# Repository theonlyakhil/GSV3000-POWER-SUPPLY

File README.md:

# GSV3000-POWER-SUPPLY

18v 30A power supply circuit diagram and KICAD files

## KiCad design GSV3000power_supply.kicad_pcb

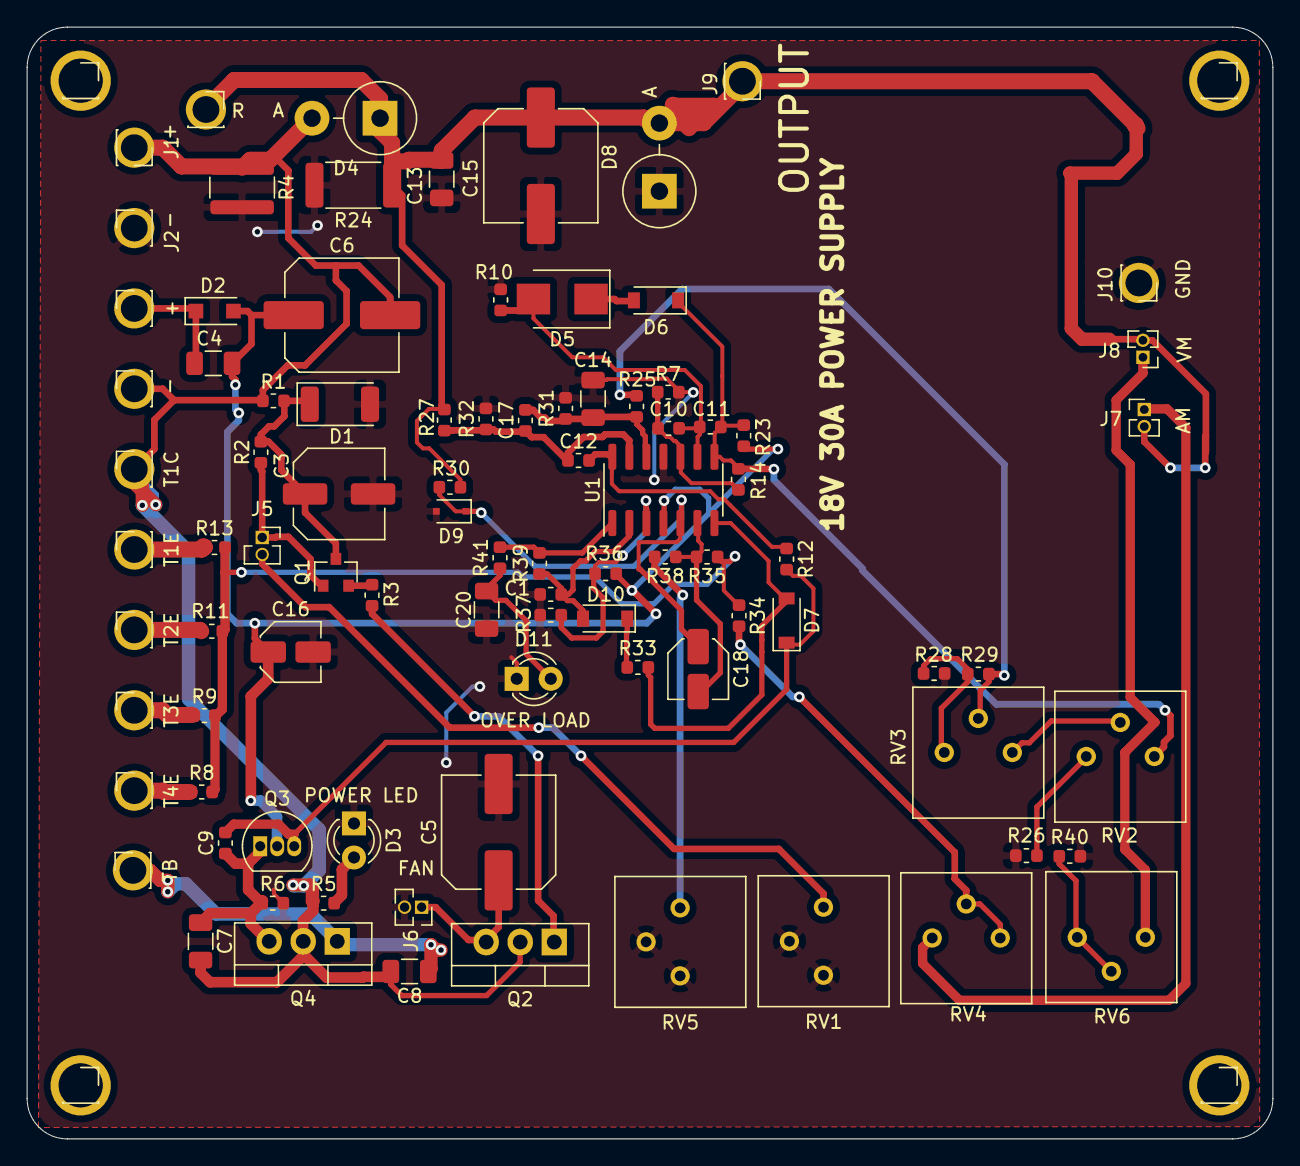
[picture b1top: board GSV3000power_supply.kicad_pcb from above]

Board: 2 copper layers, 93.0 x 83.0 mm, 94 parts (0 on the bottom side), 44 nets.

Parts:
3: 3; PinSocket_1x01_P2.54mm_Vertical
4: 4; PinSocket_1x01_P2.54mm_Vertical
C1: 1UF50V; C_0603_1608Metric
C3: 100uF; C_Elec_6.3x7.7
C4, C7, C13, C14, C20: 0.01uF; C_1206_3216Metric
C5: 220uF 25v; C_Elec_8x10.2
C6: 1000uF; C_Elec_8x10.2
C8: 0.01Uf; C_1206_3216Metric
C9: 100pF; C_0603_1608Metric
C10, C17: 22pF; C_0603_1608Metric
C11: 0.1uF; C_0603_1608Metric
C12: 0.001uF; C_0603_1608Metric
C15: 220uF 25V; C_Elec_8x10.2
C16, C18: 1uF; C_Elec_4x5.4
D1: 15V 1W; D_2010_5025Metric
D2: 1N4001; D_SOD-123F
D3: POWER LED; LED_D3.0mm
D4, D8: 1N5401; D_DO-201_P5.08mm_Vertical_AnodeUp
D5: 7.5V; D_SMB
D6, D7, D10: 1N4148; D_SOD-123
D9: 17V; D_SOD-323F
D11: OVER LOAD; LED_D3.0mm
J1, J4: +; PinSocket_1x01_P2.54mm_Vertical
J2, J3: -; PinSocket_1x01_P2.54mm_Vertical
J5: temp; PinSocket_1x02_P1.27mm_Vertical
J6: FAN; PinSocket_1x02_P1.27mm_Vertical
J7: AM; PinHeader_1x02_P1.27mm_Vertical
J8: VM; PinHeader_1x02_P1.27mm_Vertical
J9: OUTPUT; PinSocket_1x01_P2.54mm_Vertical
J10: GND; PinSocket_1x01_P2.54mm_Vertical
J11: T1C; PinSocket_1x01_P2.54mm_Vertical
J12: R; PinSocket_1x01_P2.54mm_Vertical
J15: TB; PinSocket_1x01_P2.54mm_Vertical
J16: T4E; PinSocket_1x01_P2.54mm_Vertical
J17: T3E; PinSocket_1x01_P2.54mm_Vertical
J18: T2E; PinSocket_1x01_P2.54mm_Vertical
J19: T1E; PinSocket_1x01_P2.54mm_Vertical
Q1: B550C; SOT-23
Q2: TIP31C; TO-220-3_Vertical
Q3: 2SC1815; TO-92_Inline
Q4: 2SD880; TO-220-3_Vertical
R1: 390; R_0603_1608Metric
R2: 120K; R_0603_1608Metric
R3, R7, R10, R33: 1K; R_0603_1608Metric
R4: 1K2W; R_1218_3246Metric
R5: 2.7K; R_0603_1608Metric
R6, R35: 4.7K; R_0603_1608Metric
R8: 10 X4; R_0603_1608Metric
R9, R11, R13: 10; R_0603_1608Metric
R12: 3.3K; R_0603_1608Metric
R14: 2.2K; R_0603_1608Metric
R23, R36, R37: 220K; R_0603_1608Metric
R24: 330 1W; R_2512_6332Metric
R25, R26: 5.6K; R_0603_1608Metric
R27, R32: 10K; R_0603_1608Metric
R28: 560; R_0603_1608Metric
R29: 30K; R_0603_1608Metric
R30: 1.5K; R_0603_1608Metric
R31: 1M; R_0603_1608Metric
R34: 330; R_0603_1608Metric
R38: 100K; R_0603_1608Metric
R39: 82K; R_0603_1608Metric
R40: 33K; R_0603_1608Metric
R41: 22K; R_0603_1608Metric
RV1: 50k; Potentiometer_Bourns_3386P_Vertical
RV2: 5K; Potentiometer_Bourns_3386P_Vertical
RV3, RV6: 10K; Potentiometer_Bourns_3386P_Vertical
RV4: 2K; Potentiometer_Bourns_3386P_Vertical
RV5: 50K; Potentiometer_Bourns_3386P_Vertical
S1: 1; PinSocket_1x01_P2.54mm_Vertical
S2: 2; PinSocket_1x01_P2.54mm_Vertical
U1: LM324; SOIC-14_3.9x8.7mm_P1.27mm

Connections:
GND: C1.2, C3.2, C5.2, C13.2, C14.2, C15.2, C16.2, C20.2, D1.2, D3.1, D8.1, D9.2, D11.1, J2.1, J6.2, J10.1, R4.2, R6.2, R7.2, R10.2, R24.2, R26.2, R28.2, R31.2, R32.2, R37.2, R40.2, RV1.2, RV1.3, RV5.2, RV5.3, U1.11
unnamed: C1.1, D10.2, R39.2, U1.2
unnamed: C3.1, D1.1, Q1.3, R1.2, R2.1
unnamed: C4.2, D2.1, J4.1
unnamed: C5.1, J6.1, Q2.3
unnamed: C6.2, C7.2, C8.2, D4.2, J1.1, J3.1, J11.1, Q2.2, Q4.2, R1.1, R4.1, R5.1
unnamed: C7.1, C9.1, Q3.1, Q4.3, R6.1
unnamed: C8.1, J15.1, Q4.1
unnamed: C9.2, D7.1, Q3.3, R12.2
unnamed: C10.1, R7.1, R14.2, U1.10
unnamed: C10.2, C11.2, D5.2, R10.1, U1.9
unnamed: C11.1, D6.1, R14.1, R23.2, RV2.1, U1.8
unnamed: C12.1, C17.1, R27.2, R32.1, U1.13
unnamed: C12.2, R12.1, U1.14
unnamed: C13.1, C15.1, D4.1, D8.2, J7.2, J8.2, J9.1, J12.1, R24.1, R27.1, R30.1
unnamed: C14.1, C17.2, R25.1, R31.1, U1.12
unnamed: C4.1, C6.1, C16.1, D2.2, Q3.2, R23.1, R36.1, U1.4
unnamed: C18.1, D9.1, R30.2, U1.5
unnamed: C18.2, R35.2, R38.1, U1.6
unnamed: C20.1, D11.2, R41.1
unnamed: D3.2, R5.2
unnamed: D5.1, D6.2
unnamed: D7.2, R33.2, U1.7
unnamed: D10.1, R33.1
unnamed: J5.1, Q1.1, R2.2
unnamed: J5.2, RV1.1
unnamed: J7.1, RV4.3
unnamed: J8.1, RV6.3
unnamed: J16.1, R8.1
unnamed: J17.1, R9.1
unnamed: J18.1, R11.1
unnamed: J19.1, R13.1
unnamed: Q1.2, R3.2
unnamed: Q2.1, R3.1
unnamed: R8.2, R9.2, R11.2, R13.2, R34.2, R35.1
unnamed: R25.2, R29.1, RV3.2
unnamed: R26.1, RV2.3
unnamed: R28.1, R29.2, RV3.3
unnamed: R34.1, RV4.1, RV4.2
unnamed: R36.2, R37.1, U1.3
unnamed: R38.2, RV5.1
unnamed: R39.1, R41.2, U1.1
unnamed: R40.1, RV6.1, RV6.2
unnamed: RV2.2, RV3.1
